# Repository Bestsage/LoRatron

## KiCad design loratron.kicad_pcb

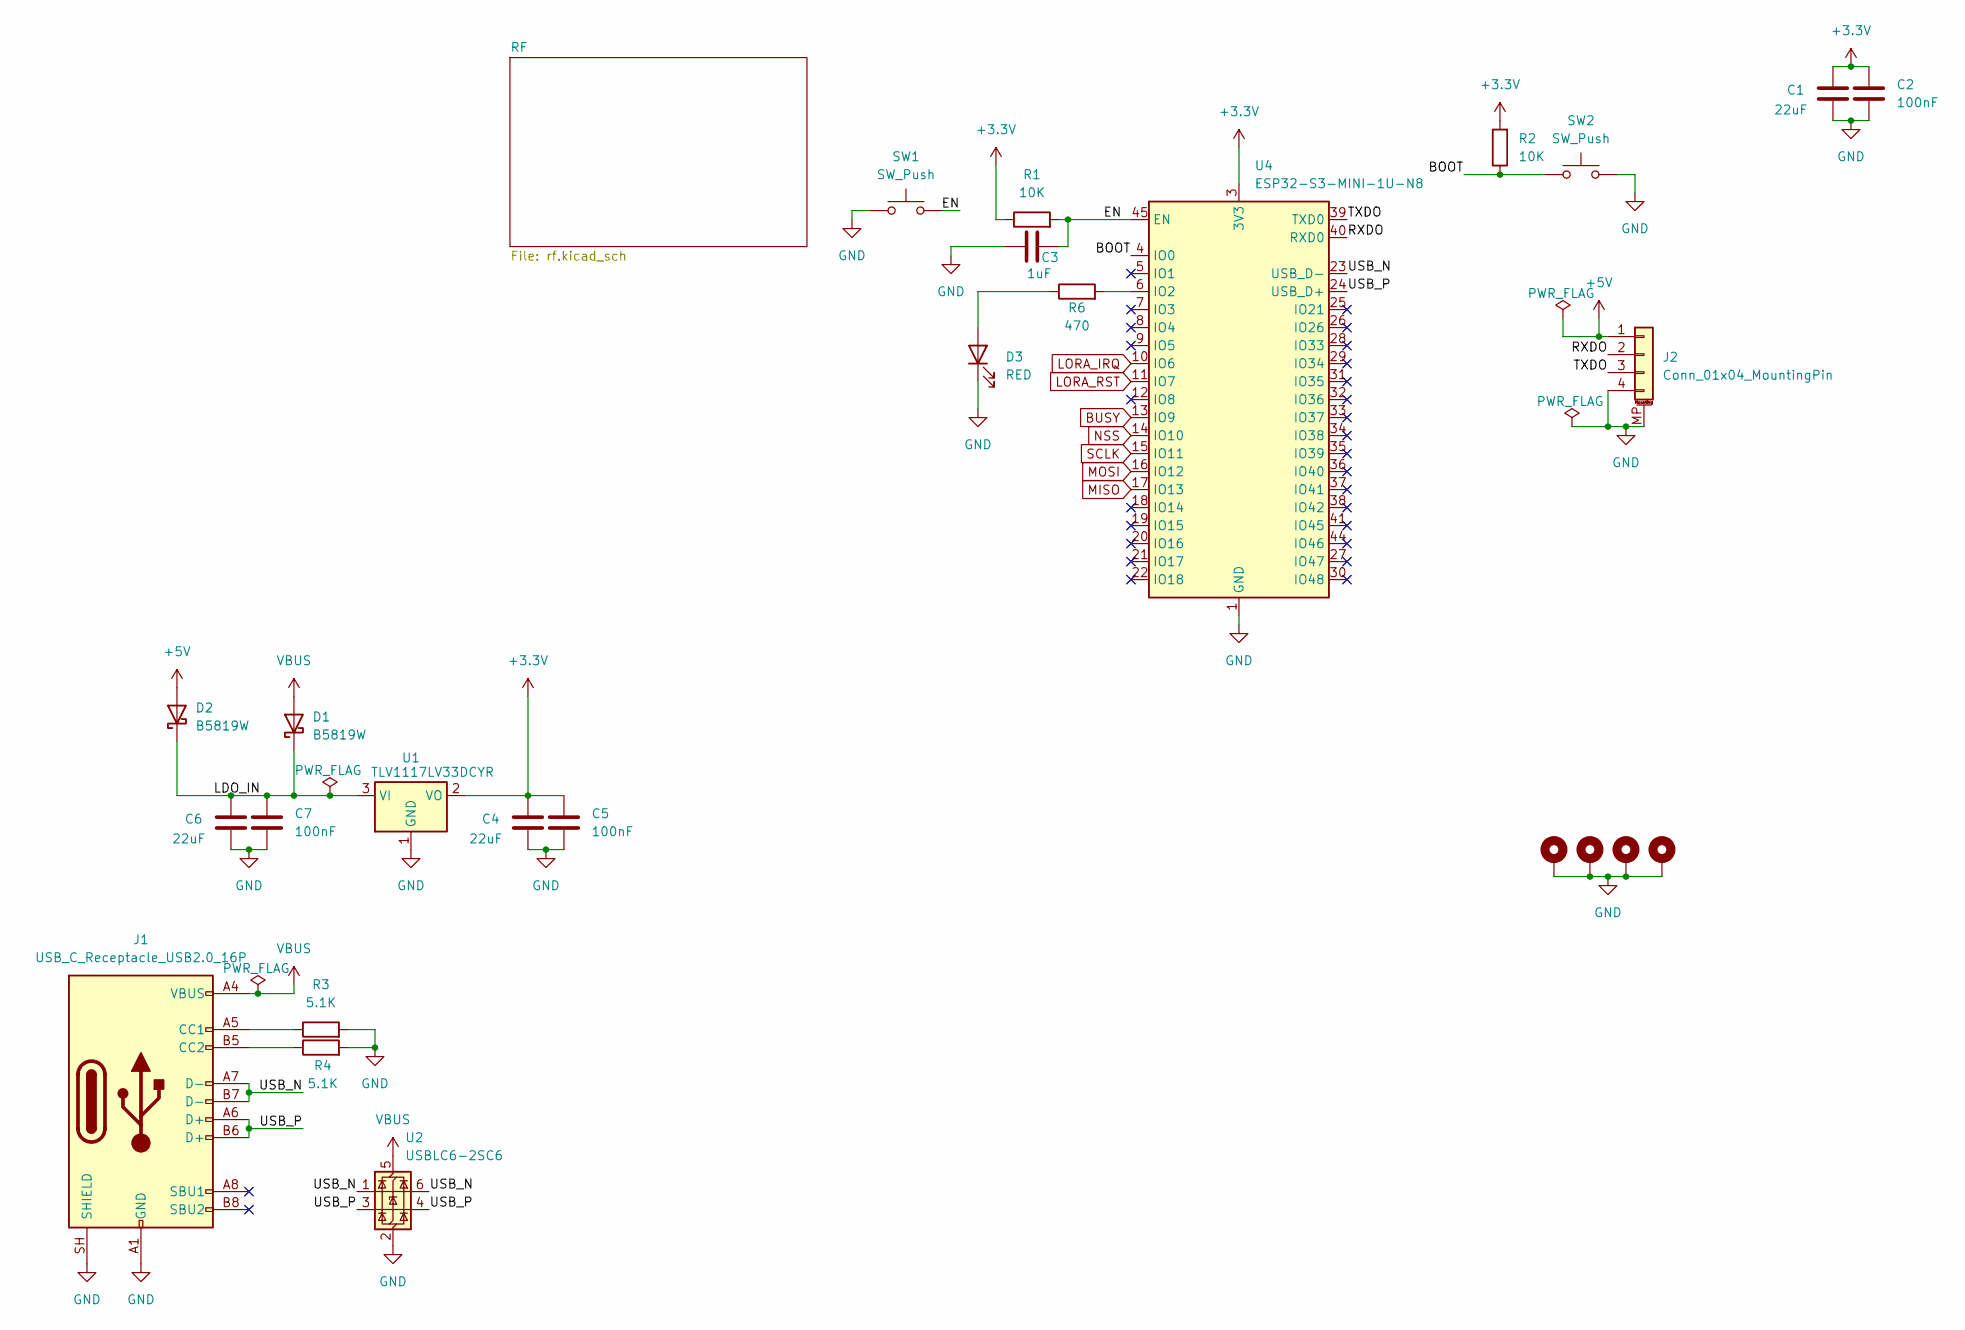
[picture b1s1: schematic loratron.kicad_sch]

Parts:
C1, C4, C6: 22uF; C_0805_2012Metric
C2, C5, C7: 100nF; C_0805_2012Metric
C3: 1uF; C_0805_2012Metric
D1, D2: B5819W; D_SOD-123
D3: RED; LED_0805_2012Metric
H1, H2, H3, H4: MountingHole_Pad; MountingHole_2.7mm_M2.5_ISO14580_Pad
J1: USB_C_Receptacle_USB2.0_16P; USB_C_Receptacle_GCT_USB4105-xx-A_16P_TopMnt_Horizontal
J2: Conn_01x04_MountingPin; JST_SH_SM04B-SRSS-TB_1x04-1MP_P1.00mm_Horizontal
R1, R2: 10K; R_0603_1608Metric
R3, R4: 5.1K; R_0603_1608Metric
R6: 470; R_0603_1608Metric
SW1, SW2: SW_Push; SW_SPST_PTS810
U1: TLV1117LV33DCYR; SOT-223-3_TabPin2
U2: USBLC6-2SC6; SOT-23-6
U4: ESP32-S3-MINI-1U-N8; ESP32-S2-MINI-1U

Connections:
+3.3V: C1.1, C2.1, C4.1, C5.1, R1.1, R2.2, U1.2 (VO), U4.3 (3V3); also elsewhere on the board
+5V: D2.2 (A), J2.1
/BOOT: R2.1, SW2.1, U4.4 (IO0)
/EN: C3.1, R1.2, SW1.2, U4.45 (EN)
/LDO_IN: C6.1, C7.1, D1.1 (K), D2.1 (K), U1.3 (VI)
/RXDO: J2.2, U4.40 (RXD0)
/TXDO: J2.3, U4.39 (TXD0)
/USB_N: J1.A7 (D-), J1.B7 (D-), U2.1 (I/O1), U2.6 (I/O1), U4.23 (USB_D-)
/USB_P: J1.A6 (D+), J1.B6 (D+), U2.3 (I/O2), U2.4 (I/O2), U4.24 (USB_D+)
BUSY: U4.13 (IO9); also elsewhere on the board
GND: C1.2, C2.2, C3.2, C4.2, C5.2, C6.2, C7.2, D3.1 (K), H1.1 (1_1), H2.1 (1_1), H3.1 (1_1), H4.1 (1_1), J1.A1 (GND), J1.A12 (GND), J1.B1 (GND), J1.B12 (GND), J1.SH (SHIELD), J2.4, J2.MP (MountPin), R3.2, R4.2, SW1.1, SW2.2, U1.1 (GND), U2.2 (GND), U4.1 (GND), U4.2 (GND), U4.42 (GND), U4.43 (GND), U4.46 (GND), U4.47 (GND), U4.48 (GND), U4.49 (GND), U4.50 (GND), U4.51 (GND), U4.52 (GND), U4.53 (GND), U4.54 (GND), U4.55 (GND), U4.56 (GND), U4.57 (GND), U4.58 (GND), U4.59 (GND), U4.60 (GND), U4.61 (GND), U4.62 (GND), U4.63 (GND), U4.64 (GND), U4.65 (GND); also elsewhere on the board
LORA_IRQ: U4.10 (IO6); also elsewhere on the board
LORA_RST: U4.11 (IO7); also elsewhere on the board
MISO: U4.17 (IO13); also elsewhere on the board
MOSI: U4.16 (IO12); also elsewhere on the board
NSS: U4.14 (IO10); also elsewhere on the board
unnamed: D3.2 (A), R6.1
unnamed: J1.A5 (CC1), R3.1
unnamed: J1.B5 (CC2), R4.1
unnamed: R6.2, U4.6 (IO2)
SCLK: U4.15 (IO11); also elsewhere on the board
VBUS: D1.2 (A), J1.A4 (VBUS), J1.A9 (VBUS), J1.B4 (VBUS), J1.B9 (VBUS), U2.5 (VBUS)

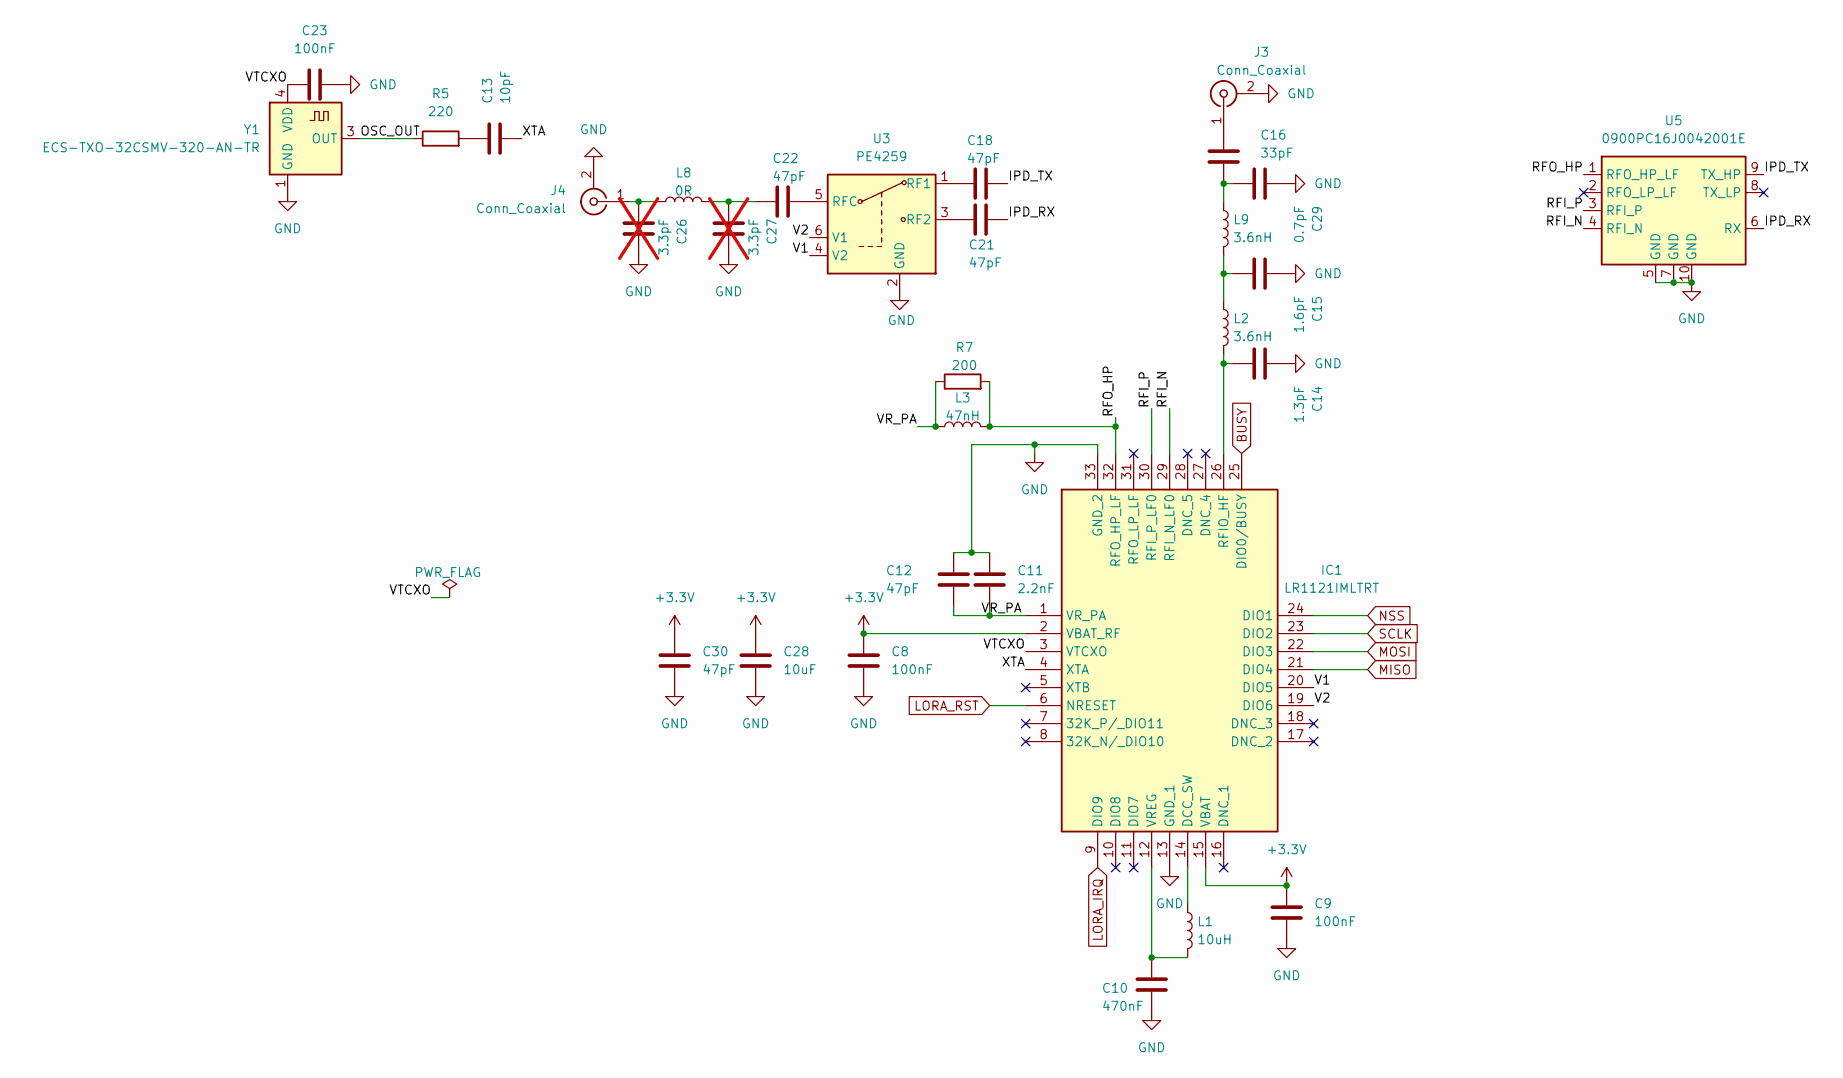
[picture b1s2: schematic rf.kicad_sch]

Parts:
C8, C9, C23: 100nF; C_0402_1005Metric
C10: 470nF; C_0402_1005Metric
C11: 2.2nF; C_0402_1005Metric
C12, C18, C21, C22, C30: 47pF; C_0402_1005Metric
C13: 10pF; C_0402_1005Metric
C14: 1.3pF; C_0402_1005Metric
C15: 1.6pF; C_0402_1005Metric
C16: 33pF; C_0402_1005Metric
C26, C27: 3.3pF; C_0402_1005Metric; not fitted
C28: 10uF; C_0603_1608Metric
C29: 0.7pF; C_0402_1005Metric
IC1: LR1121IMLTRT; QFN50P500X500X100-33N-D; Mouser Part Number 947-LR1121IMLTRT
J3, J4: Conn_Coaxial; U.FL_Hirose_U.FL-R-SMT-1_Vertical
L1: 10uH; L_0603_1608Metric
L2, L9: 3.6nH; L_0402_1005Metric
L3: 47nH; L_0402_1005Metric
L8: 0R; L_0402_1005Metric
R5: 220; R_0402_1005Metric
R7: 200; R_0402_1005Metric
U3: PE4259; SOT-363_SC-70-6
U5: 0900PC16J0042001E; Johanson_IPD_0900PC16J0042001E; MPN 0900PC16J0042001E; DigiKey 712-0900PC16J0042001ECT-ND
Y1: ECS-TXO-32CSMV-320-AN-TR; Crystal_SMD_3225-4Pin_3.2x2.5mm

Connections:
+3.3V: C8.2, C9.2, C28.2, C30.2, IC1.2 (VBAT_RF), IC1.15 (VBAT); also elsewhere on the board
/RF/IPD_RX: C21.1, U5.6 (RX)
/RF/IPD_TX: C18.2, U5.9 (TX_HP)
/RF/OSC_OUT: R5.1, Y1.3 (OUT)
/RF/RFI_N: IC1.29 (RFI_N_LF0), U5.4 (RFI_N)
/RF/RFI_P: IC1.30 (RFI_P_LF0), U5.3 (RFI_P)
/RF/RFO_HP: IC1.32 (RFO_HP_LF), L3.2, R7.2, U5.1 (RFO_HP_LF)
/RF/V1: IC1.20 (DIO5), U3.4 (V2)
/RF/V2: IC1.19 (DIO6), U3.6 (V1)
/RF/VR_PA: C11.1, C12.1, IC1.1 (VR_PA), L3.1, R7.1
/RF/VTCXO: C23.2, IC1.3 (VTCXO), Y1.4 (VDD)
/RF/XTA: C13.1, IC1.4 (XTA)
BUSY: IC1.25 (DIO0/BUSY); also elsewhere on the board
GND: C8.1, C9.1, C10.1, C11.2, C12.2, C14.2, C15.2, C23.1, C26.1, C27.1, C28.1, C29.2, C30.1, IC1.13 (GND_1), IC1.33 (GND_2), J3.2 (Ext), J4.2 (Ext), U3.2 (GND), U5.5 (GND), U5.7 (GND), U5.10 (GND), Y1.1 (GND), Y1.2 (GND); also elsewhere on the board
LORA_IRQ: IC1.9 (DIO9); also elsewhere on the board
LORA_RST: IC1.6 (NRESET); also elsewhere on the board
MISO: IC1.21 (DIO4); also elsewhere on the board
MOSI: IC1.22 (DIO3); also elsewhere on the board
NSS: IC1.24 (DIO1); also elsewhere on the board
unnamed: C13.2, R5.2
unnamed: C15.1, L2.1, L9.2
unnamed: C16.1, C29.1, L9.1
unnamed: C22.2, C27.2, L8.2
unnamed: IC1.14 (DCC_SW), L1.1
unnamed: C14.1, IC1.26 (RFIO_HF), L2.2
unnamed: C10.2, IC1.12 (VREG), L1.2
unnamed: C16.2, J3.1 (In)
unnamed: C26.2, J4.1 (In), L8.1
unnamed: C18.1, U3.1 (RF1)
unnamed: C21.2, U3.3 (RF2)
unnamed: C22.1, U3.5 (RFC)
SCLK: IC1.23 (DIO2); also elsewhere on the board

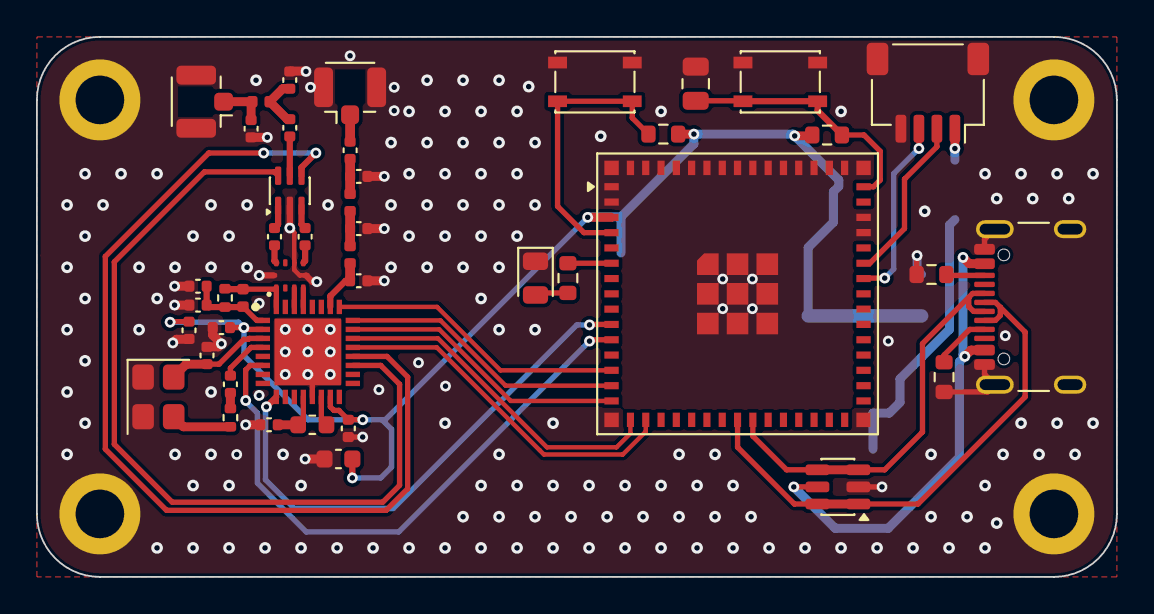
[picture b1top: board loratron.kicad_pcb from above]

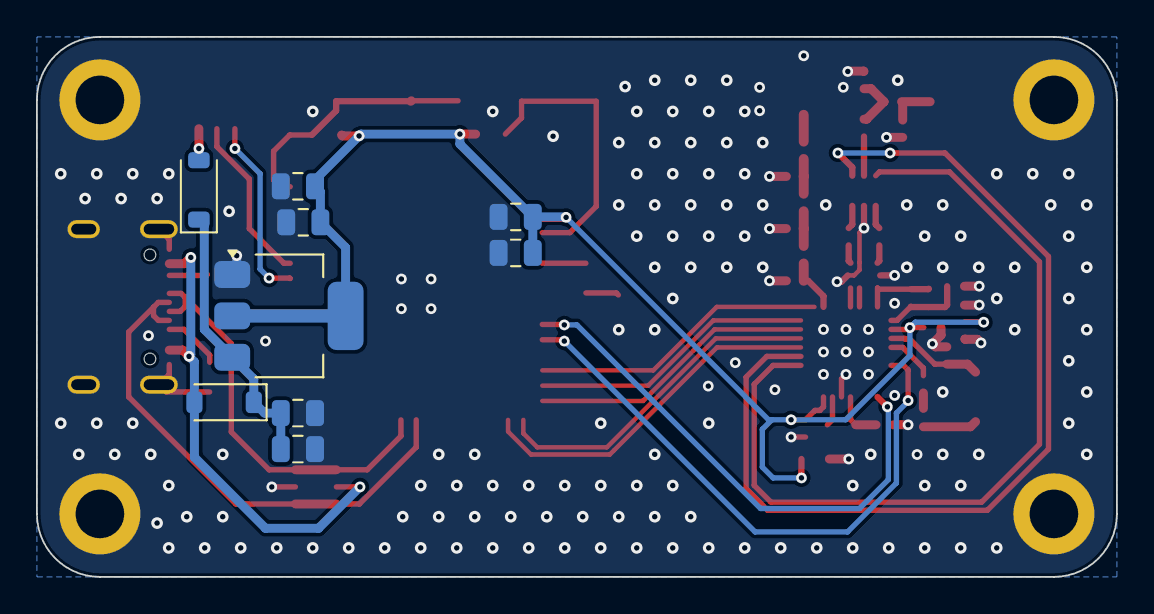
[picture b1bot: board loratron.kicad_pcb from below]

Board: 2 copper layers, 60.0 x 30.0 mm, 57 parts (9 on the bottom side), 45 nets.

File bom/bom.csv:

Reference,Qty,Value,Footprint,MPN,Manufacturer,DigiKey,DK_Stock,Mouser,MO_Stock,LCSC,LC_Stock,Chosen_Distributor,Datasheet,Validated,DNP,Notes
C3,1,1uF,0805,GRM21BR71E105KA99L,Murata Electronics,,,,,C77080,10100,LCSC,,,,
"C4,C1,C6",3,22uF,0805,GRM21BR61E226ME44L,Murata Electronics,,,,,C86816,0,LCSC,,,,
"C7,C2,C5",3,100nF,0805,GRM21BR71H104KA01L,Murata Electronics,,,,,C77082,192250,LCSC,,,,
C10,1,470nF,0402,GRM155R61A474KE15D,Murata Electronics,,,,,C77003,33950,LCSC,,,,
C11,1,2.2nF,0402,GRM155R71H222KA01D,Murata Electronics,,,,,C77022,52200,LCSC,,,,
C13,1,10pF,0402,GRM1555C1H100JA01D,Murata Electronics,,,,,C76946,297800,LCSC,,,,
C14,1,1.3pF,0402,GJM1555C1H1R3WB01D,Murata Electronics,,,,,C88880,18060,LCSC,,,,"GRM1555C1H1R3BA01D (±0.1 pF, NRND) is an acceptable substitute"
C15,1,1.6pF,0402,GJM1555C1H1R6BB01D,Murata Electronics,,,,,C161311,7840,LCSC,,,,
C16,1,33pF,0402,GRM1555C1H330GA01D,Murata Electronics,,,,,C162097,8700,LCSC,,,,±2% version; GRM1555C1H330JA01D is NRND
"C23,C8,C9",3,100nF,0402,GRM155R71C104KA88D,Murata Electronics,,,,,C71629,1000000,LCSC,,,,
"C26,C27",2,3.3pF,0402,GJM1555C1H3R3BB01D,Murata Electronics,,,,,C76906,170350,,,,yes,DNP - tuning spare
C28,1,10uF,0603,GRM188R61A106ME69D,Murata Electronics,,,,,C90053,120000,LCSC,,,,
C29,1,0.7pF,0402,GJM1555C1HR70BB01D,Murata Electronics,,,,,C161349,14900,LCSC,,,,
"C30,C18,C21,C22,C12",5,47pF,0402,GRM1555C1H470JA01D,Murata Electronics,,,,,C76970,29300,LCSC,,,,
"D1,D2",2,B5819W,SOD-123,B5819W-TP,Micro Commercial Co,,,,,C84354,49860,LCSC,,,,
D3,1,RED,0805,LTST-C171KRKT,Lite-On,,,,,C284871,59800,LCSC,,,,
IC1,1,LR1121IMLTRT,QFN50P500X500X100-33N-D,LR1121IMLTRT,Semtech,,,947-LR1121IMLTRT,,C7498014,2480,LCSC,https://semtech.my.salesforce.com/sfc/p/#E0000000JelG/a/3n00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,,,
J1,1,USB_C_Receptacle_USB2.0_16P,USB_C_Receptacle_GCT_USB4105-xx-A_16P_TopMnt_Horizontal,USB4105-GF-A,GCT,,,,,C3020560,0,LCSC,https://www.usb.org/sites/default/files/documents/usb_type-c.zip,,,
J2,1,Conn_01x04_MountingPin,JST_SH_SM04B-SRSS-TB_1x04-1MP_P1.00mm_Horizontal,SM04B-SRSS-TB(LF)(SN),JST,,,,,C160404,55510,LCSC,,,,
"J4,J3",2,Conn_Coaxial,U.FL_Hirose_U.FL-R-SMT-1_Vertical,U.FL-R-SMT-1(10),Hirose,,,,,C88373,34615,LCSC,,,,
L1,1,10uH,0603,MLZ1608N100LT000,TDK,,,,,C194437,19430,LCSC,,,,
L3,1,47nH,0402,LQW15AN47NJ00D,Murata Electronics,,,,,C192855,7250,LCSC,,,,
L8,1,0R,0402,RC0402JR-070RL,YAGEO,,,,,C60485,8882000,LCSC,,,,0R jumper in L_0402 footprint (tuning placeholder)
"L9,L2",2,3.6nH,0402,LQW15AN3N6C10D,Murata Electronics,,,,,C408158,6840,LCSC,,,,
"R1,R2",2,10K,0603,RC0603FR-0710KL,YAGEO,,,,,C98220,5006500,LCSC,,,,
"R3,R4",2,5.1K,0603,RC0603FR-075K1L,YAGEO,,,,,C105580,5101200,LCSC,,,,
R5,1,220,0402,RC0402FR-07220RL,YAGEO,,,,,C112291,2699200,LCSC,,,,
R6,1,470,0603,RC0603FR-07470RL,YAGEO,,,,,C114669,666700,LCSC,,,,
R7,1,200,0402,RC0402FR-07200RL,YAGEO,,,,,C114764,61900,LCSC,,,,
"SW2,SW1",2,SW_Push,SW_SPST_PTS810,PTS810SJM250SMTRLFS,C&K,,,,,C116501,0,LCSC,,,,
U1,1,TLV1117LV33DCYR,SOT-223-3_TabPin2,TLV1117LV33DCYR,Texas Instruments,,,,,C15578,0,LCSC,https://www.ti.com/lit/gpn/tlv1117lv,,,
U2,1,USBLC6-2SC6,SOT-23-6,USBLC6-2SC6,STMicroelectronics,,,,,C7519,36815,LCSC,https://www.st.com/resource/en/datasheet/usblc6-2.pdf,,,
U3,1,PE4259,SOT-363_SC-70-6,PE4259-63,pSemi,1046-1011-1-ND,,,,C470892,12715,LCSC,,,,
U4,1,ESP32-S3-MINI-1U-N8,ESP32-S2-MINI-1U,ESP32-S3-MINI-1U-N8,Espressif Systems,,,,,C2980299,2353,LCSC,https://www.espressif.com/sites/default/files/documentation/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,,,
U5,1,0900PC16J0042001E,Johanson_IPD_0900PC16J0042001E,0900PC16J0042001E,Johanson Technology,712-0900PC16J0042001ECT-ND,,,,C19842466,0,LCSC,https://www.johansontechnology.com/docs/3812/IPD-0900PC16J00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,,,
Y1,1,ECS-TXO-32CSMV-320-AN-TR,Crystal_SMD_3225-4Pin_3.2x2.5mm,ECS-TXO-32CSMV-320-AN-TR,ECS Inc.,,,,,,,,https://ecsxtal.com/store/pdf/ECS-TXO-32CSMV.pdf,,,
